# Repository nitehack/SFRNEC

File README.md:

SFRNEC
======
This is a printable robot. 
It is a simple robot upgradeable. An example is included in the repository to control the robot via a IR remote control.

Authors
-------
Made for
* Víctor Burgos González
* Nicolás Guerrero García (Nitehack)
* Alejandro Toral López
* Pedro Manuel Vallejo Muñoz

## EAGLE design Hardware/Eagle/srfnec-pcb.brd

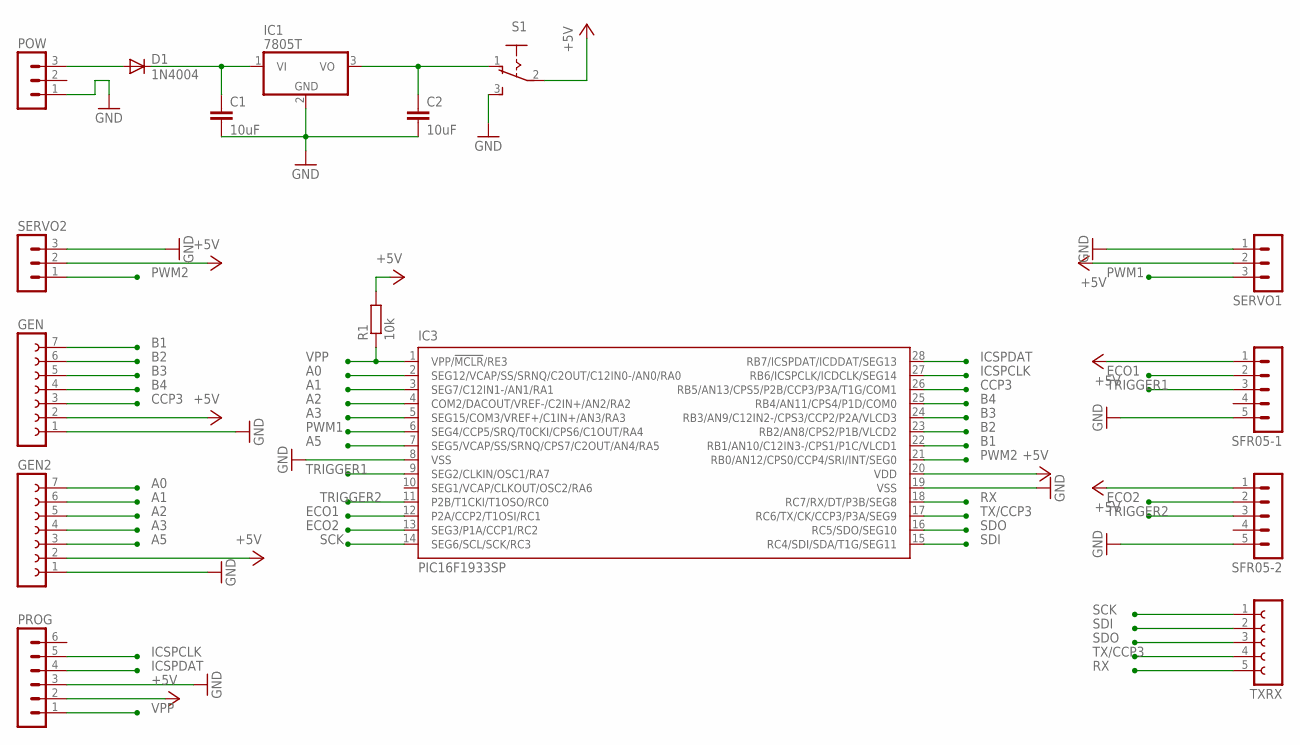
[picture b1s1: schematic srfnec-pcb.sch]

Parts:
C1, C2: 10uF; C5B2.5
D1: 1N4004; DO41-10
GEN, GEN2: FE07-1; FE07
IC1: 7805T; TO220H
IC3: PIC16F1933SP; DIL28-3
POW: MA03-1
PROG: MA06-1
R1: 10k; 0204/7
S1: 255SB
SERVO1, SERVO2: MA03-1
SFR05-1, SFR05-2: MA05-1
TXRX: FE05-1

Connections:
+5V: GEN.2, GEN2.2, IC3.20 (VDD), PROG.2, R1.2, S1.2, SERVO1.2, SERVO2.2, SFR05-1.1, SFR05-2.1
A0: GEN2.7, IC3.2 (SEG12/VCAP/SS/SRNQ/C2OUT/C12IN0-/AN0/RA0)
A1: GEN2.6, IC3.3 (SEG7/C12IN1-/AN1/RA1)
A2: GEN2.5, IC3.4 (COM2/DACOUT/VREF-/C2IN+/AN2/RA2)
A3: GEN2.4, IC3.5 (SEG15/COM3/VREF+/C1IN+/AN3/RA3)
A5: GEN2.3, IC3.7 (SEG5/VCAP/SS/SRNQ/CPS7/C2OUT/AN4/RA5)
B1: GEN.7, IC3.22 (RB1/AN10/C12IN3-/CPS1/P1C/VLCD1)
B2: GEN.6, IC3.23 (RB2/AN8/CPS2/P1B/VLCD2)
B3: GEN.5, IC3.24 (RB3/AN9/C12IN2-/CPS3/CCP2/P2A/VLCD3)
B4: GEN.4, IC3.25 (RB4/AN11/CPS4/P1D/COM0)
CCP3: GEN.3, IC3.26 (RB5/AN13/CPS5/P2B/CCP3/P3A/T1G/COM1)
ECO1: IC3.12 (P2A/CCP2/T1OSI/RC1), SFR05-1.2
ECO2: IC3.13 (SEG3/P1A/CCP1/RC2), SFR05-2.2
GND: C1.2, C2.2, GEN.1, GEN2.1, IC1.2 (GND), IC3.8 (VSS), IC3.19 (VSS), POW.1, PROG.3, S1.3 (S), SERVO1.1, SERVO2.3, SFR05-1.5, SFR05-2.5
ICSPCLK: IC3.27 (RB6/ICSPCLK/ICDCLK/SEG14), PROG.5
ICSPDAT: IC3.28 (RB7/ICSPDAT/ICDDAT/SEG13), PROG.4
unnamed: C1.1, D1.C, IC1.1 (VI)
unnamed: D1.A, POW.3
unnamed: C2.1, IC1.3 (VO), S1.1 (O)
PWM1: IC3.6 (SEG4/CCP5/SRQ/T0CKI/CPS6/C1OUT/RA4), SERVO1.3
PWM2: IC3.21 (RB0/AN12/CPS0/CCP4/SRI/INT/SEG0), SERVO2.1
RX: IC3.18 (RC7/RX/DT/P3B/SEG8), TXRX.5
SCK: IC3.14 (SEG6/SCL/SCK/RC3), TXRX.1
SDI: IC3.15 (RC4/SDI/SDA/T1G/SEG11), TXRX.2
SDO: IC3.16 (RC5/SDO/SEG10), TXRX.3
TRIGGER1: IC3.9 (SEG2/CLKIN/OSC1/RA7), SFR05-1.3
TRIGGER2: IC3.11 (P2B/T1CKI/T1OSO/RC0), SFR05-2.3
TX/CCP3: IC3.17 (RC6/TX/CK/CCP3/P3A/SEG9), TXRX.4
VPP: IC3.1 (VPP/!MCLR!/RE3), PROG.1, R1.1

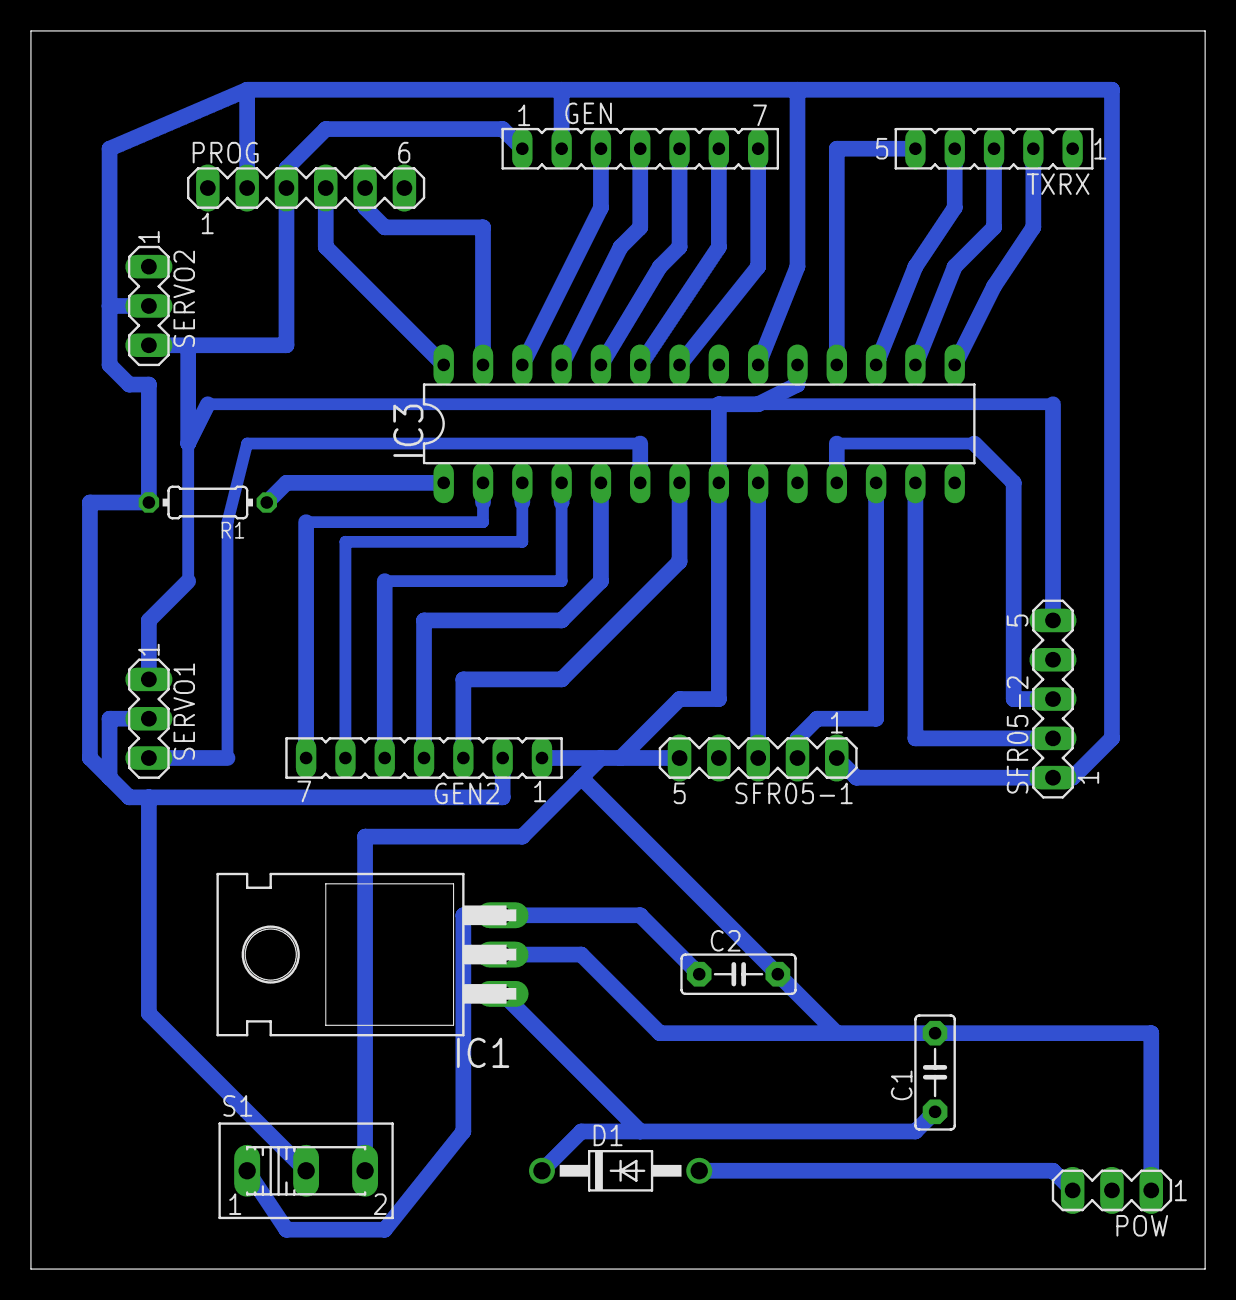
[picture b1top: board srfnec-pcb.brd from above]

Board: 2 copper layers, 75.9 x 80.0 mm, 16 parts (0 on the bottom side), 29 nets.

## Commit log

2014-02-22 Part
2014-02-23 media
2014-02-23 change
2014-02-23 no define
2014-02-23 ir module
